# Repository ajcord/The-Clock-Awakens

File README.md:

The Clock Awakens
=================

Using LEDs and an ESP8266 to make a smart, futuristic Star Wars clock

See [the project page](https://hackaday.io/project/7681-the-clock-awakens)
for details such as the parts list, building instructions, etc.

Uses the [Sunrise-Sunset API](http://sunrise-sunset.org/api) among others.

Setting up the environment
--------------------------

1. Set up the ESP8266 in the Arduino IDE
   ([instructions](https://github.com/esp8266/Arduino))
2. Install the [Time](https://github.com/PaulStoffregen/Time),
   [Adafruit NeoPixel](https://github.com/adafruit/Adafruit_NeoPixel),
   [WiFiManager](https://github.com/tzapu/WiFiManager), and
   [ESP8266Scheduler](https://github.com/nrwiersma/ESP8266Scheduler)
   libraries through the Library Manager
   ([instructions](https://www.arduino.cc/en/Guide/Libraries#toc3))
3. Install the
   [ESP8266FS tool](https://github.com/esp8266/arduino-esp8266fs-plugin)
   located in `lib`
   ([instructions](http://arduino.esp8266.com/versions/1.6.5-1160-gef26c5f/doc/reference.html#uploading-files-to-file-system))
4. Make the necessary changes to `src/firmware/config.h.template`
    and save them in `src/firmware/config.h`
5. Open `src/firmware/firmware.ino` in the Arduino IDE
6. Upload the sketch data by going to Tools > ESP8266 Sketch Data Upload
7. Upload the sketch to the device

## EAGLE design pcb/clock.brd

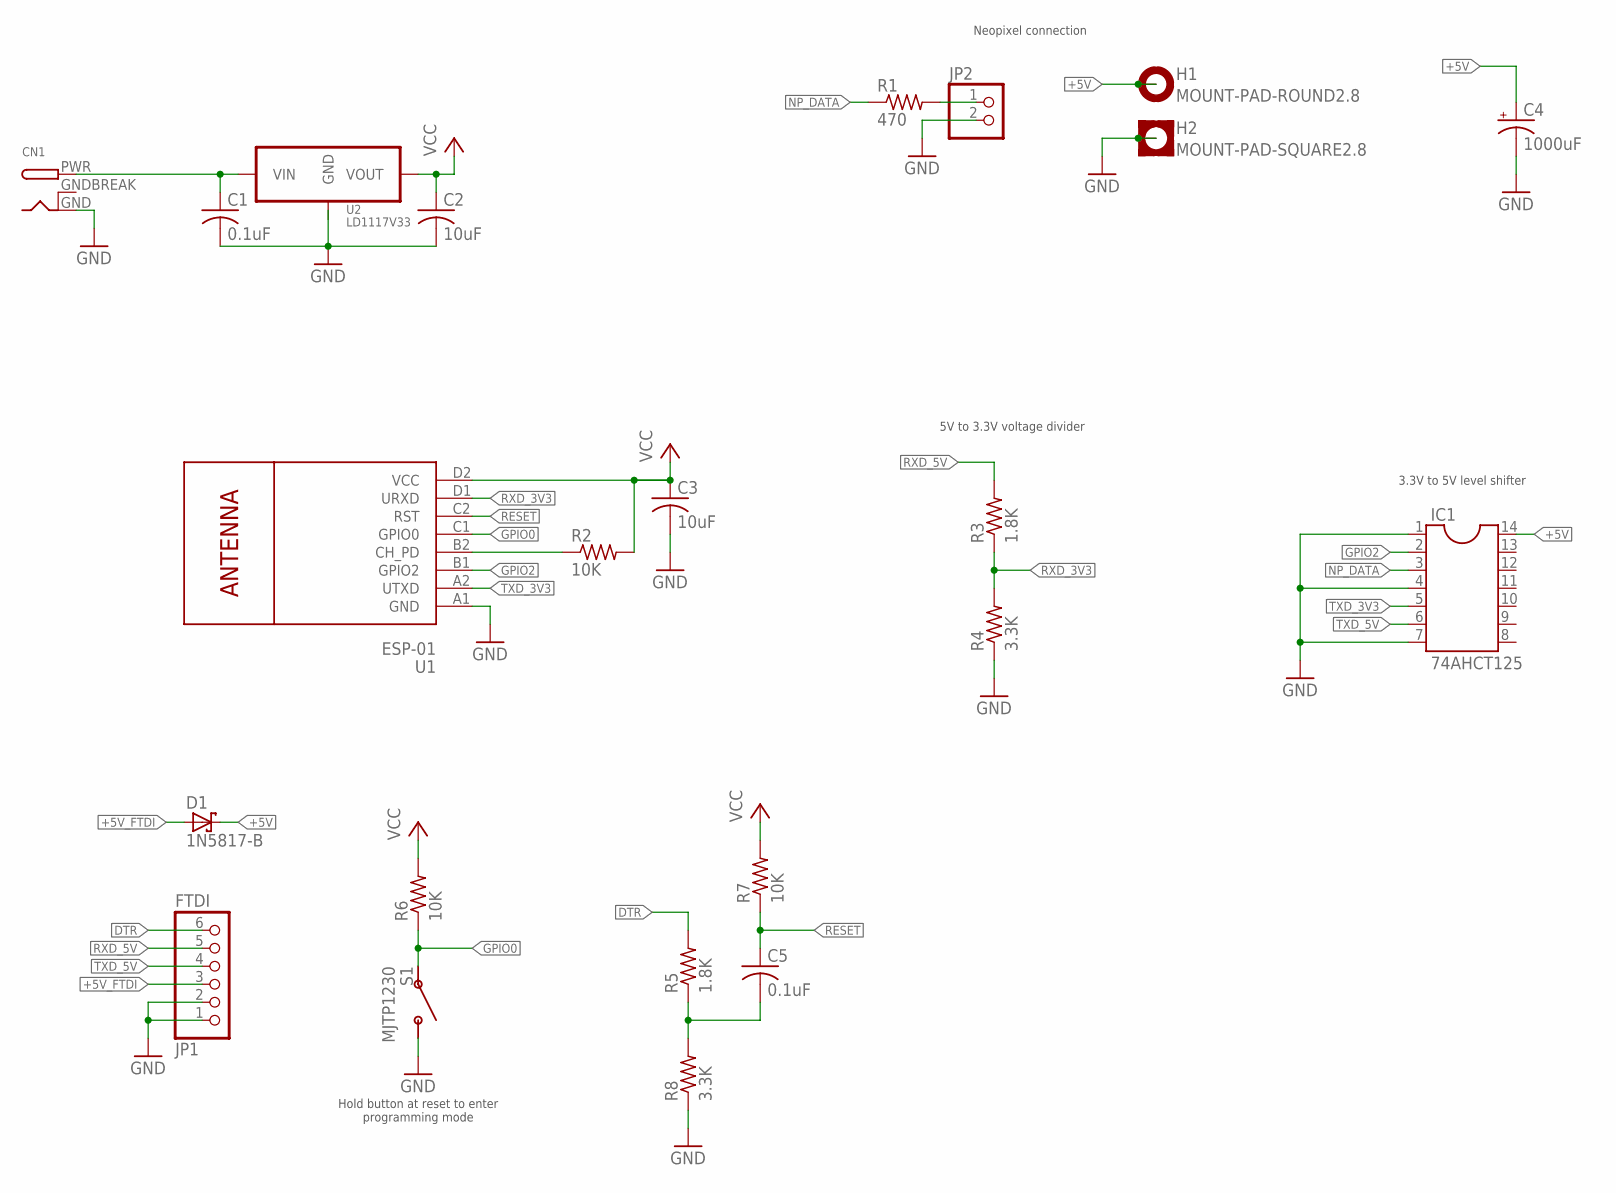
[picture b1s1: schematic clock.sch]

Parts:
C1, C5: 0.1uF; C025-025X050
C2, C3: 10uF; C025-025X050
C4: 1000uF; E3,5-8
CN1: DCBARRELPTH; DCJACK_2MM_PTH
D1: 1N5817-B; DO41-7.6
H1: MOUNT-PAD-ROUND2.8; 2,8-PAD
H2: MOUNT-PAD-SQUARE2.8; 2,8-PAD-SQUARE
IC1: 74AHCT125; DIL14
JP1: FTDI; 1X06/90
JP2: PINHD-1X2; 1X02
R1: 470; 0204/5
R2, R6, R7: 10K; 0204/5
R3, R5: 1.8K; 0204/5
R4, R8: 3.3K; 0204/5
S1: MJTP1230; TACTILE-BUTTON-MJTP1230
U1: ESP-01; WIRELESS-WIFI-ESP-01
U2: LD1117V33; TO-220

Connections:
+5V: C1.1, C4.+, CN1.PWR, D1.C, H1.B2,8, IC1.14, U2.P$3 (VIN)
+5V_FTDI: D1.A, JP1.3
DTR: JP1.6, R5.2
GND: C1.2, C2.2, C3.2, C4.-, CN1.GND, H2.B2,8, IC1.1, IC1.4, IC1.7, JP1.1, JP1.2, JP2.2, R4.1, R8.1, S1.P$2 (3), S1.P$4 (3), U1.A1 (GND), U2.P$1 (GND)
GNDBREAK: CN1.GNDBREAK
GPIO0: R6.1, S1.P$1 (1), S1.P$3 (1), U1.C1 (GPIO0)
GPIO2: IC1.2, U1.B1 (GPIO2)
unnamed: JP2.1, R1.2
unnamed: C5.2, R5.1, R8.2
unnamed: R2.1, U1.B2 (CH_PD)
NP_DATA: IC1.3, R1.1
RESET: C5.1, R7.1, U1.C2 (RST)
RXD_3V3: R3.1, R4.2, U1.D1 (URXD)
RXD_5V: JP1.5, R3.2
TXD_3V3: IC1.5, U1.A2 (UTXD)
TXD_5V: IC1.6, JP1.4
VCC: C2.1, C3.1, R2.2, R6.2, R7.2, U1.D2 (VCC), U2.P$2 (VOUT), U2.P$4 (VOUT)

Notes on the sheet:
Hold button at reset to enter programming mode
5V to 3.3V voltage divider
3.3V to 5V level shifter
Neopixel connection

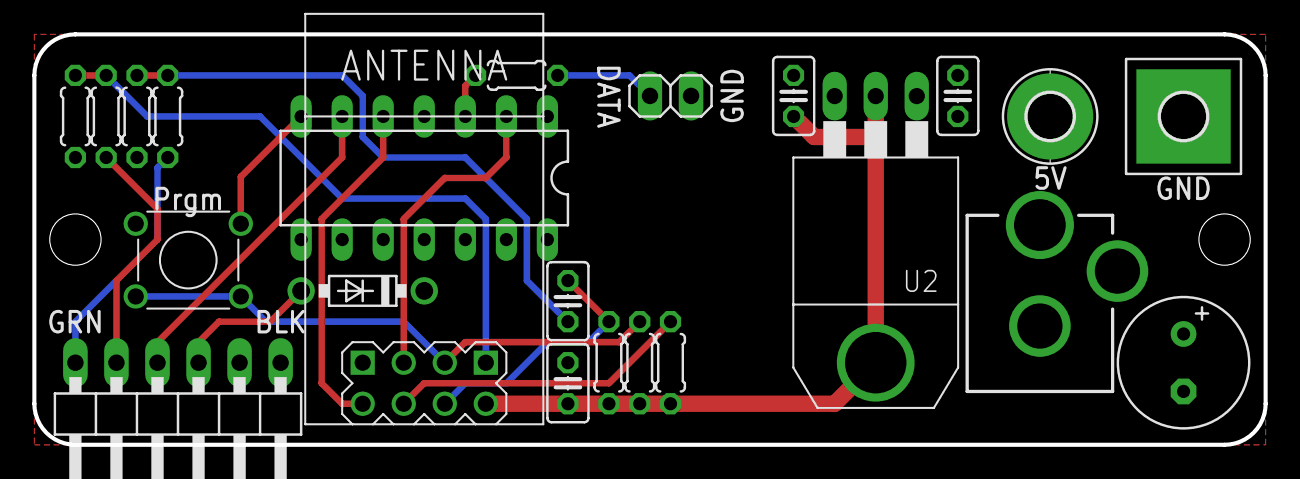
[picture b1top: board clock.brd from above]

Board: 2 copper layers, 76.2 x 25.4 mm, 23 parts (0 on the bottom side), 16 nets.

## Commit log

2016-09-03 Fade down before sunset instead of after
2016-09-03 Updated for Arduino IDE 1.6.10
2016-09-03 Added scheduler, waiting on library to stabilize
2016-09-03 Fixed panics, but web server always refuses connections due to clock display task
2016-09-03 Removed backward MAC address workaround
2016-09-03 Added empty PCB design
2016-09-04 Started PCB
2016-09-18 Added button
2016-09-19 Linearized the board layout
2016-09-19 Improved layout to make room for light sensor
2016-09-19 Added RP diode, tweaked layout
2016-09-19 Replaced 1N4004 with 1N5817
2016-09-19 Added DTR to RST pin
2016-09-20 Changed resistor size & voltage divider values
2016-09-20 Minor adjustments

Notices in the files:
parts and their libraries:
diy-modules: Released under the Creative Commons Attribution 4.0 International License: http://creativecommons.org/licenses/by/4.0
